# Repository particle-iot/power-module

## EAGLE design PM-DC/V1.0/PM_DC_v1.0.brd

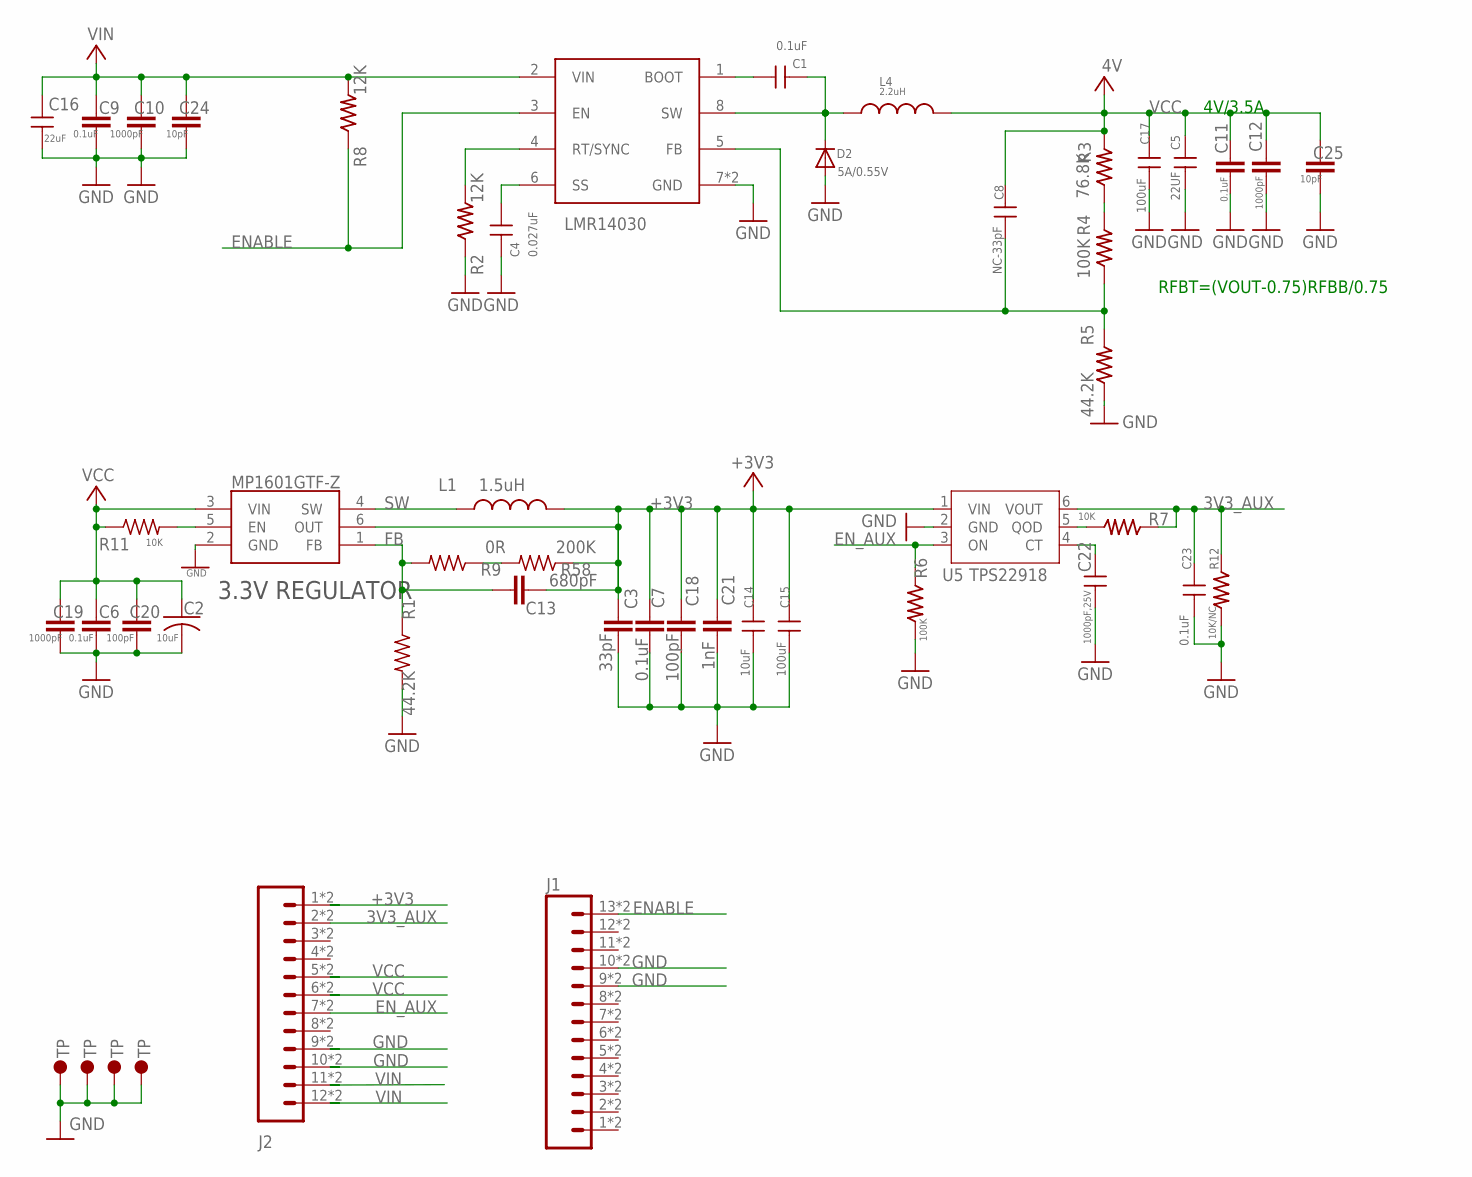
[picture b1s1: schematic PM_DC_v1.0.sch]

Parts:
C1: 0.1uF; C0402
C2: 10uF; C0603_B
C3: 33pF; C0402_B
C4: 0.027uF; C0402
C5: 22UF; C0805
C6, C7, C9, C11: 0.1uF; C0402_B
C8: NC-33pF; C0402
C10, C12, C19: 1000pF; C0402_B
C13: 680pF; C0402_B
C14: 10uF; C0805
C15, C17: 100uF; C1206
C16: 22uF; C805
C18, C20: 100pF; C0402_B
C21: 1nF; C0402_B
C22: 1000pF,25V; C0402
C23: 0.1uF; C-0402
C24, C25: 10pF; C0402_B
D2: 5A/0.55V; SMADIODE
J1: M13PTH-CST-R; 1X13-CASTELLATED
J2: M12PTH-CST-R; 1X12-CASTELLATED
L1: 1.5uH; INDUCTOR-2520
L4: 2.2uH; INDUCTOR-4040
R1: 44.2K; R0402_B
R2, R8: 12K; R-0402S
R3: 76.8K; R-0402S
R4: 100K; R-0402S
R5: 44.2K; R-0402S
R6: 100K; R0402
R7: 10K; R0402
R9: 0R; R0402_B
R11: 10K; R0402_B
R12: 10K/NC; R0402
R58: 200K; R0402_B
U2: LMR14030; SO_POWERPAD_8
U3: MP1601GTF-Z; SOTFL50P160X60-6N
U5: TPS22918; SOT-23-6
U$1, U$2, U$4, U$5: TP; TP_2.33X1.37

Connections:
3V3_AUX: C23.1, J2.2, J2.@2 (2), R7.1, R12.1, U5.6 (VOUT)
+3V3: C3.2, C7.2, C13.1, C14.1, C15.1, C18.2, C21.2, J2.1, J2.@1 (1), L1.2, R58.1, U3.6 (OUT), U5.1 (VIN)
ENABLE: J1.13, J1.@13 (13), R8.1, U2.3 (EN)
EN_AUX: J2.7, J2.@7 (7), R6.1, U5.3 (ON)
FB: C13.2, R1.1, R9.2, U3.1 (FB)
GND: C2.2, C3.1, C4.2, C5.2, C6.1, C7.1, C9.1, C10.1, C11.1, C12.1, C14.2, C15.2, C16.2, C17.2, C18.1, C19.1, C20.1, C21.1, C22.2, C23.2, C24.1, C25.1, D2.A, J1.9, J1.10, J1.@9 (9), J1.@10 (10), J2.9, J2.10, J2.@9 (9), J2.@10 (10), R1.2, R2.1, R5.1, R6.2, R12.2, U2.7 (GND), U2.EP (GND), U3.2 (GND), U5.2 (GND), U$1.1, U$2.1, U$4.1, U$5.1
unnamed: R7.2, U5.5 (QOD)
unnamed: C8.1, R4.1, R5.2, U2.5 (FB)
unnamed: R11.2, U3.5 (EN)
unnamed: R9.1, R58.2
unnamed: C4.1, U2.6 (SS)
unnamed: C1.2, D2.C, L4.P$1 (1), U2.8 (SW)
unnamed: C1.1, U2.1 (BOOT)
unnamed: R2.2, U2.4 (RT/SYNC)
unnamed: R3.1, R4.2
unnamed: C22.1, U5.4 (CT)
SW: L1.1, U3.4 (SW)
VCC: C2.1, C5.1, C6.2, C8.2, C11.2, C12.2, C17.1, C19.2, C20.2, C25.2, J2.5, J2.6, J2.@5 (5), J2.@6 (6), L4.P$2 (2), R3.2, R11.1, U3.3 (VIN)
VIN: C9.2, C10.2, C16.1, C24.2, J2.11, J2.12, J2.@11 (11), J2.@12 (12), R8.2, U2.2 (VIN)

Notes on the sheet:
4V/3.5A
3.3V REGULATOR
RFBT=(VOUT-0.75)RFBB/0.75

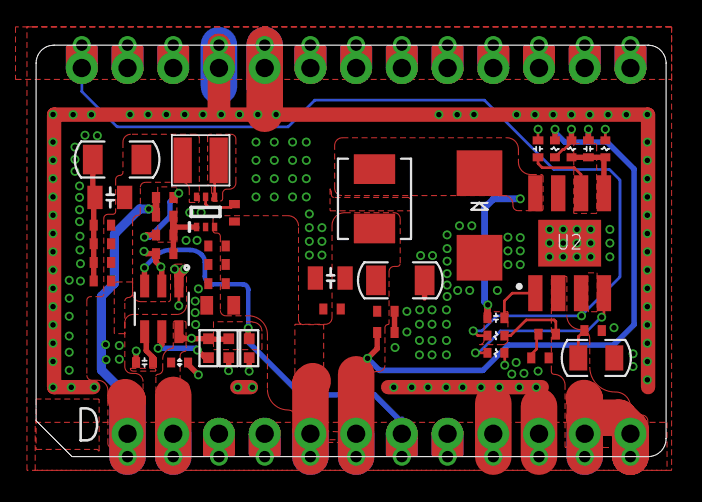
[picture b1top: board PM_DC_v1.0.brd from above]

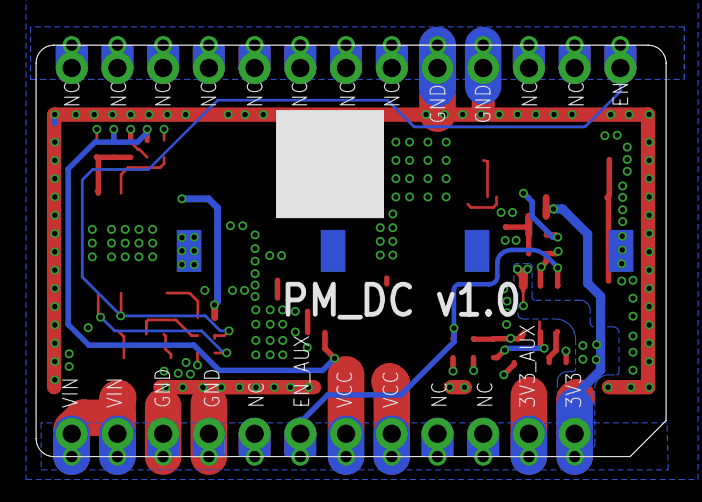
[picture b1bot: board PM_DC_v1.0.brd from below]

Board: 2 copper layers, 35.0 x 22.9 mm, 49 parts (4 on the bottom side), 19 nets.

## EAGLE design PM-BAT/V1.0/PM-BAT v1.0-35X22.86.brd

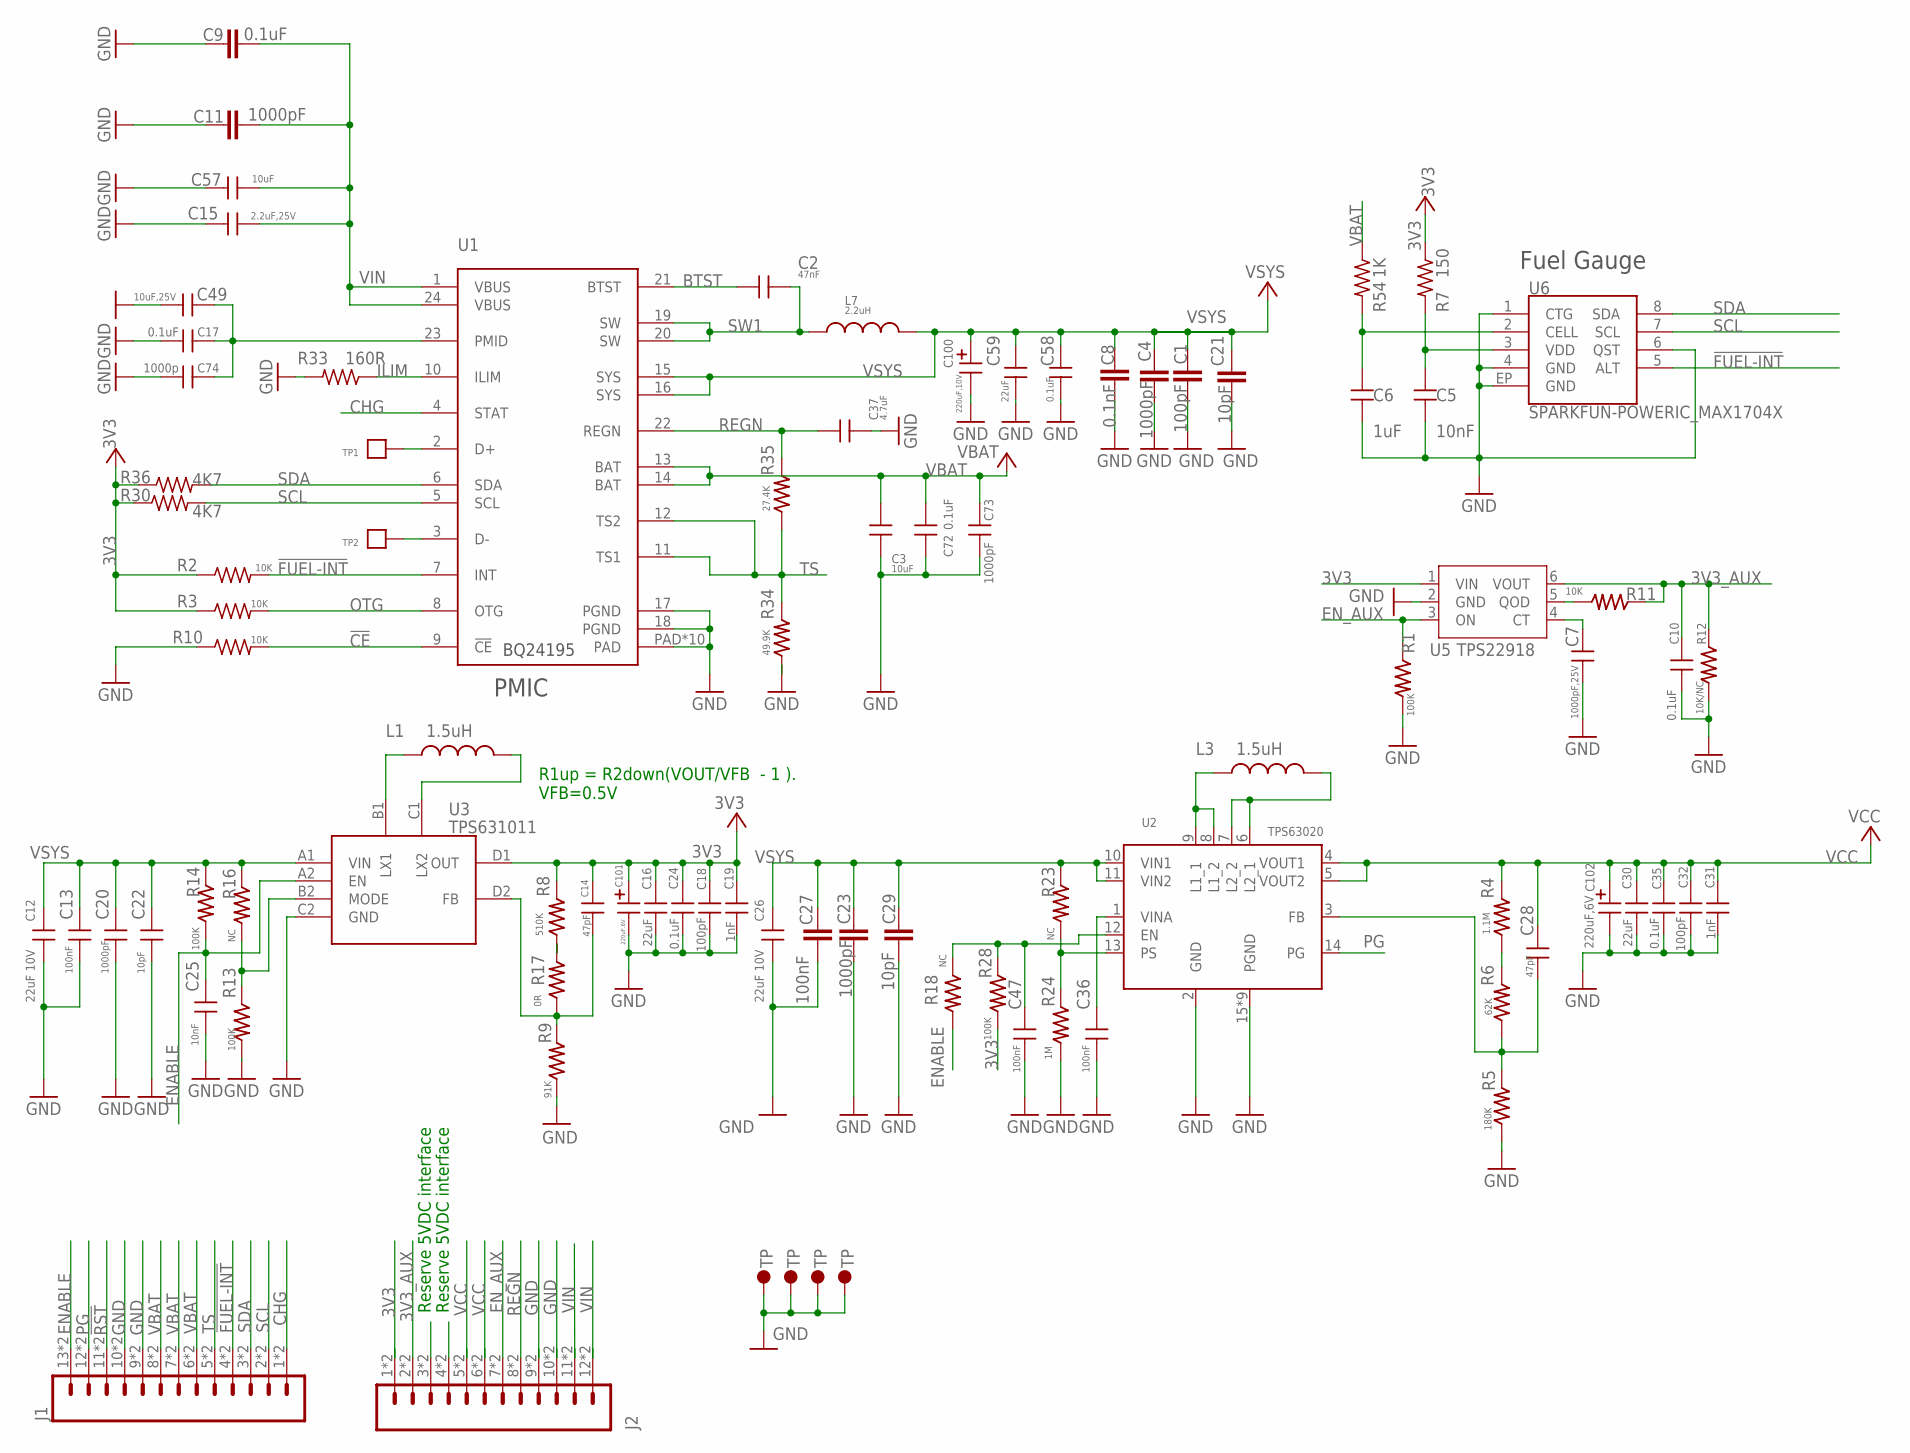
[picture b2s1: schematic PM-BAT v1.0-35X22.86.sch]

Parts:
C1: 100pF; C0402_B
C2: 47nF; C-0402
C3: 10uF; C0805
C4, C11, C23: 1000pF; C0402_B
C5: 10nF; C0402
C6: 1uF; C0402
C7: 1000pF,25V; C0402
C8: 0.1nF; C0402_B
C9: 0.1uF; C0402_B
C10: 0.1uF; C0201-N
C12, C26: 22uF 10V; C0603
C13, C36, C47: 100nF; C0201-N
C14, C28: 47pF; C0201-N
C15: 2.2uF,25V; C-0603A
C16, C30: 22uF; C-0603A
C17, C24, C35, C58: 0.1uF; C0402
C18, C32: 100pF; C0402
C19, C31: 1nF; C0402
C20: 1000pF; C0201-N
C21, C29: 10pF; C0402_B
C22: 10pF; C0201-N
C25: 10nF; C0201-N
C27: 100nF; C0402_B
C37: 4.7uF; C0402
C49: 10uF,25V; C-0603A
C57: 10uF; C-0603A
C59: 22uF; C0603
C72: 0.1uF; C-0402
C73: 1000pF; C-0402
C74: 1000p; C-0402
C100: 220uF,10V; CASE-B
C101: 220uF.6V; CASE-B
C102: 220uF,6V; CASE-B
J1: M13PTH-CST-R; 1X13-CASTELLATED
J2: M12PTH-CST-R; 1X12-CASTELLATED
L1, L3: 1.5uH; INDUCTOR-2520
L7: 2.2uH; INDUCTOR-4040
R1, R13, R14, R28: 100K; R0201-N
R2, R3, R10: 10K; R0402_B
R4: 1.1M; R0201-N
R5: 180K; R0201-N
R6: 62K; R0201-N
R7: 150; R0402_B
R8: 510K; R0201-N
R9: 91K; R0201-N
R11: 10K; R0201-N
R12: 10K/NC; R0201-N
R16, R18, R23: NC; R0201-N
R17: 0R; R0201-N
R24: 1M; R0201-N
R30, R36: 4K7; R0402_B
R33: 160R; R0402_B
R34: 49.9K; R0201-N
R35: 27.4K; R0201-N
R54: 1K; R0402_B
TP1, TP2: TP1311MM; TP-1311MM
U1: BQ24195; ELECTRON_QFN24
U2: TPS63020
U3: TPS631011; DSBGA
U5: TPS22918; SOT-23-6
U6: SPARKFUN-POWERIC_MAX1704X; SPARKFUN-POWERIC_TDFN-8
U$1, U$2, U$4, U$5: TP; TP_2.33X1.37

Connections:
3V3: C14.1, C16.1, C18.1, C19.1, C24.1, C101.P$1 (1), J2.1, J2.@1 (1), R2.1, R3.1, R7.1, R8.2, R28.2, R30.1, R36.1, U3.D1 (OUT), U5.1 (VIN)
3V3_AUX: C10.1, J2.2, J2.@2 (2), R11.1, R12.1, U5.6 (VOUT)
!CE: R10.2, U1.9 (!CE)
!FUEL-INT: J1.4, J1.@4 (4), R2.2, U1.7 (INT), U6.5 (ALT)
!RST: J1.11, J1.@11 (11)
BTST: C2.1, U1.21 (BTST)
CHG: J1.1, J1.@1 (1), U1.4 (STAT)
ENABLE: C25.1, J1.13, J1.@13 (13), R14.2, R18.2, U3.A2 (EN)
EN_AUX: J2.7, J2.@7 (7), R1.1, U5.3 (ON)
GND: C1.1, C3.2, C4.1, C5.2, C6.2, C7.2, C8.1, C9.1, C10.2, C11.1, C12.2, C13.2, C15.2, C16.2, C17.1, C18.2, C19.2, C20.2, C21.1, C22.2, C23.1, C24.2, C25.2, C26.2, C27.1, C29.1, C30.2, C31.2, C32.2, C35.2, C36.2, C37.2, C47.2, C49.2, C57.2, C58.2, C59.2, C72.2, C73.2, C74.1, C100.P$2 (2), C101.P$2 (2), C102.P$2 (2), J1.9, J1.10, J1.@9 (9), J1.@10 (10), J2.9, J2.10, J2.@9 (9), J2.@10 (10), R1.2, R5.1, R9.1, R10.1, R12.2, R13.2, R24.2, R33.2, R34.1, U1.17 (PGND), U1.18 (PGND), U1.PAD, U1.PAD@1 (PAD), U1.PAD@2 (PAD), U1.PAD@3 (PAD), U1.PAD@4 (PAD), U1.PAD@5 (PAD), U1.PAD@6 (PAD), U1.PAD@7 (PAD), U1.PAD@8 (PAD), U1.PAD@9 (PAD), U2.2 (GND), U2.15 (PGND), U2.16 (PGND), U2.17 (PGND), U2.18 (PGND), U2.19 (PGND), U2.20 (PGND), U2.21 (PGND), U2.22 (PGND), U2.23 (PGND), U3.C2 (GND), U5.2 (GND), U6.1 (CTG), U6.4 (GND), U6.6 (QST), U6.EP (GND), U$1.1, U$2.1, U$4.1, U$5.1
ILIM: R33.1, U1.10 (ILIM)
unnamed: J2.3, J2.@3 (3)
unnamed: C17.2, C49.1, C74.2, U1.23 (PMID)
unnamed: TP2.P$1, U1.3 (D-)
unnamed: C14.2, R9.2, R17.1, U3.D2 (FB)
unnamed: C28.2, R5.2, R6.1, U2.3 (FB)
unnamed: TP1.P$1, U1.2 (D+)
unnamed: R8.1, R17.2
unnamed: R4.1, R6.2
unnamed: J2.4, J2.@4 (4)
unnamed: L3.1, U2.8 (L1_2), U2.9 (L1_1)
unnamed: L1.1, U3.B1 (LX1)
unnamed: R13.1, R16.2, U3.B2 (MODE)
unnamed: L3.2, U2.6 (L2_1), U2.7 (L2_2)
unnamed: L1.2, U3.C1 (LX2)
unnamed: C7.1, U5.4 (CT)
unnamed: C36.1, U2.1 (VINA)
unnamed: R11.2, U5.5 (QOD)
unnamed: C47.1, R18.1, R28.1, U2.12 (EN)
unnamed: R23.2, R24.1, U2.13 (PS)
unnamed: C5.1, R7.2, U6.3 (VDD)
unnamed: C6.1, R54.2, U6.2 (CELL)
OTG: R3.2, U1.8 (OTG)
PG: J1.12, J1.@12 (12), U2.14 (PG)
REGN: C37.1, J2.8, J2.@8 (8), R35.2, U1.22 (REGN)
SCL: J1.2, J1.@2 (2), R30.2, U1.5 (SCL), U6.7 (SCL)
SDA: J1.3, J1.@3 (3), R36.2, U1.6 (SDA), U6.8 (SDA)
SW1: C2.2, L7.P$1 (1), U1.19 (SW), U1.20 (SW)
TS: J1.5, J1.@5 (5), R34.2, R35.1, U1.11 (TS1), U1.12 (TS2)
VBAT: C3.1, C72.1, C73.1, J1.6, J1.7, J1.8, J1.@6 (6), J1.@7 (7), J1.@8 (8), R54.1, U1.13 (BAT), U1.14 (BAT)
VCC: C28.1, C30.1, C31.1, C32.1, C35.1, C102.P$1 (1), J2.5, J2.6, J2.@5 (5), J2.@6 (6), R4.2, U2.4 (VOUT1), U2.5 (VOUT2)
VIN: C9.2, C11.2, C15.1, C57.1, J2.11, J2.12, J2.@11 (11), J2.@12 (12), U1.1 (VBUS), U1.24 (VBUS)
VSYS: C1.2, C4.2, C8.2, C12.1, C13.1, C20.1, C21.2, C22.1, C23.2, C26.1, C27.2, C29.2, C58.1, C59.1, C100.P$1 (1), L7.P$2 (2), R14.1, R16.1, R23.1, U1.15 (SYS), U1.16 (SYS), U2.10 (VIN1), U2.11 (VIN2), U3.A1 (VIN)

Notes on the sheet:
PMIC
Fuel Gauge
R1up = R2down(VOUT/VFB - 1 ). VFB=0.5V
Reserve 5VDC interface

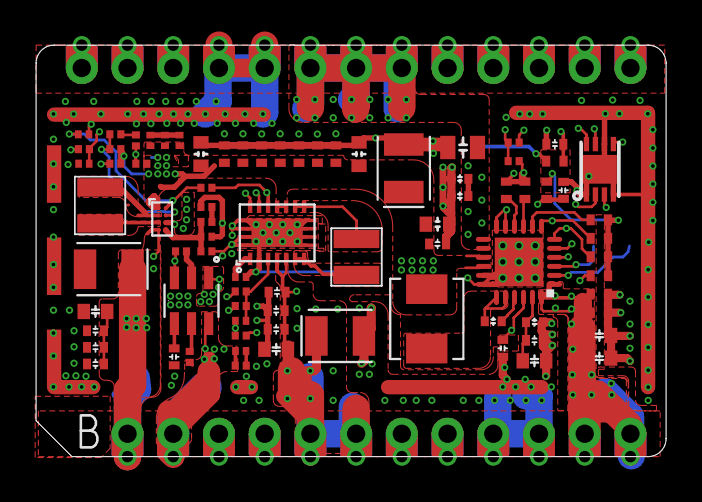
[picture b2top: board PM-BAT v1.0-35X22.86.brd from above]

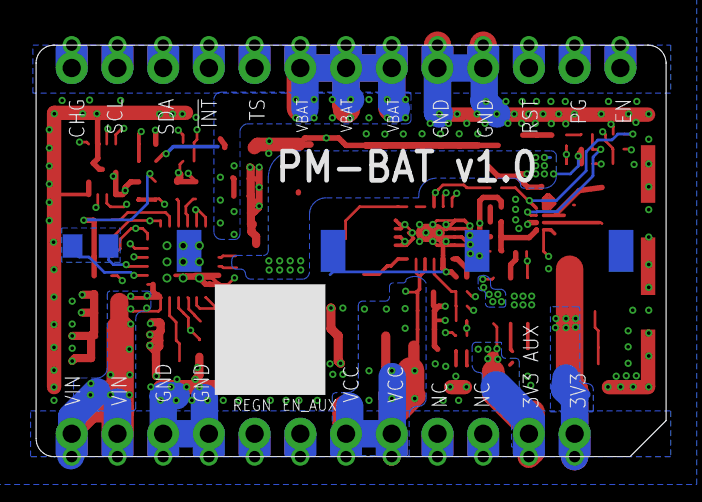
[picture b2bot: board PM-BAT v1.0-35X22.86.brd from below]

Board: 4 copper layers, 35.0 x 22.9 mm, 88 parts (6 on the bottom side), 43 nets.

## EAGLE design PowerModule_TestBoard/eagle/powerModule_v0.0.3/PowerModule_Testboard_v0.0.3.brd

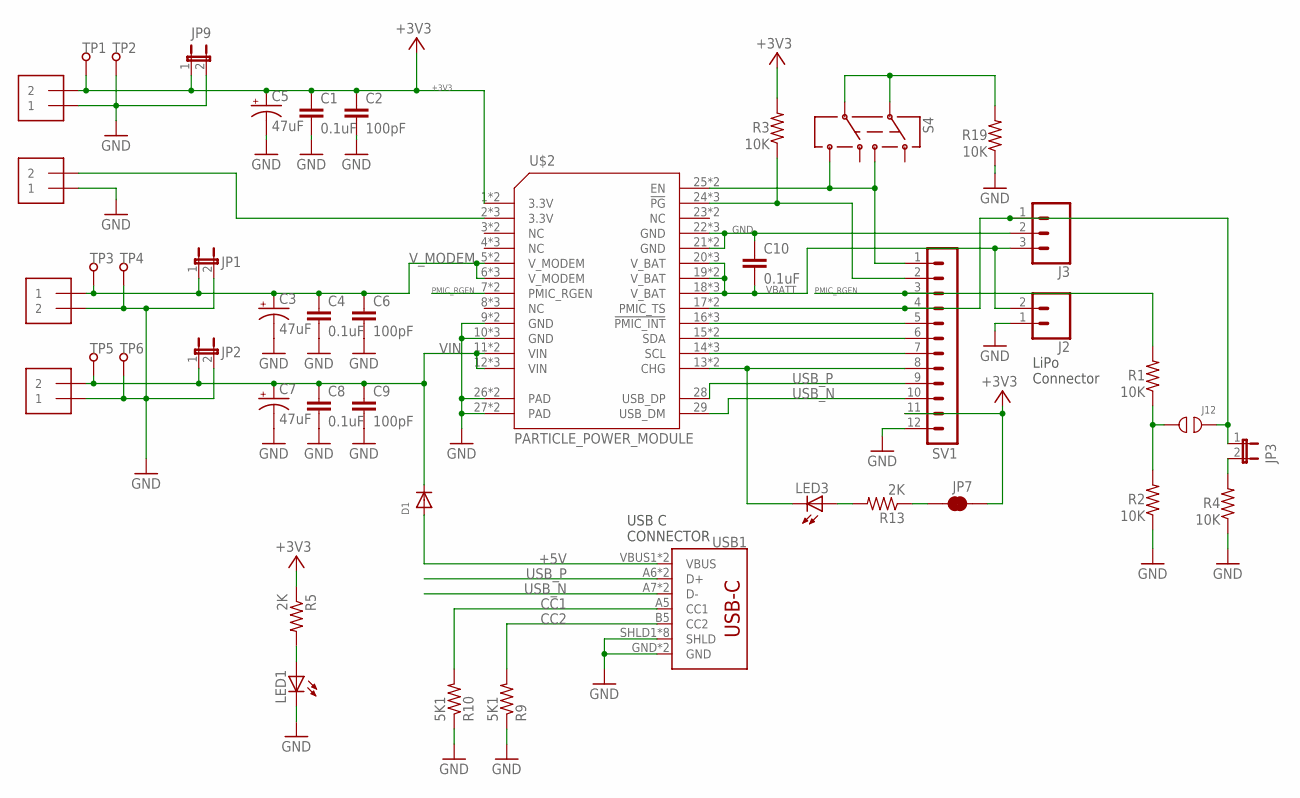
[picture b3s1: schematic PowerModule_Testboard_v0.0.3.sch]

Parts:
C1, C4, C8, C10: 0.1uF; 0603
C2, C6, C9: 100pF; 0603
C3, C5, C7: 47uF; NIC_10X10.5_CAP
D1: DIODE_SOD-123FL; SOD-123FL
J1, J4, J5, J6: 1X2-3.5MM
J2: CONN_02-JST-2MM-SMT; JST-2-SMD@2
J3: CONN_03JST-SMD-VERT; JST-3-SMD-VERT
J12: TP_OPEN
JP1, JP2, JP3, JP9: JUMPER2
JP7: JUMPER-SMT_2_NC_TRACE_NO-SILK; SMT-JUMPER_2_NC_TRACE_NO-SILK
LED1, LED3: LEDCHIP-LED0603; CHIP-LED0603
R1, R2, R3, R4, R19: 10K; R0603_P
R5, R13: 2K; R0603_P
R9, R10: 5K1; R0603_P
S4: SWITCH-DPDT; SWITCH-2.5X3.2-6
SV1: MA12-1
TP1, TP2, TP3, TP4, TP5, TP6: TP-S2751-46R; S2751-46R
U$2: PARTICLE_POWER_MODULE
USB1: USB_C16PIN; USB-C-16P

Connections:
+3V3: C1.1, C2.1, C5.+, J4.2, JP7.1, JP9.1, R3.2, R5.1, SV1.11, TP1.1, U$2.1 (3.3V), U$2.1@1 (3.3V)
+5V: D1.A, USB1.VBUS1 (VBUS), USB1.VBUS2 (VBUS)
CC1: R10.2, USB1.A5 (CC1)
CC2: R9.2, USB1.B5 (CC2)
GND: C1.2, C2.2, C3.-, C4.2, C5.-, C6.2, C7.-, C8.2, C9.2, C10.1, J1.2, J2.1 (2), J3.2, J4.1, J5.1, J6.1, JP1.2, JP2.2, JP9.2, LED1.C, R2.1, R4.1, R9.1, R10.1, R19.1, SV1.12, TP2.1, TP4.1, TP6.1, U$2.9 (GND), U$2.9@1 (GND), U$2.10 (GND), U$2.10@1 (GND), U$2.10@2 (GND), U$2.21 (GND), U$2.21@1 (GND), U$2.22 (GND), U$2.22@1 (GND), U$2.22@2 (GND), U$2.26 (PAD), U$2.26@1 (PAD), U$2.27 (PAD), U$2.27@2 (PAD), USB1.GND, USB1.GND2 (GND), USB1.SHLD1 (SHLD), USB1.SHLD2 (SHLD), USB1.SHLD3 (SHLD), USB1.SHLD4 (SHLD), USB1.SHLD5 (SHLD), USB1.SHLD6 (SHLD), USB1.SHLD7 (SHLD), USB1.SHLD8 (SHLD)
unnamed: JP7.2, R13.1
unnamed: R19.2, S4.2, S4.5
unnamed: J12.1, R1.1, R2.2
unnamed: R3.1, SV1.2, U$2.24 (!PG), U$2.24@1 (!PG), U$2.24@2 (!PG)
unnamed: J3.1, J12.2, JP3.1, SV1.4, U$2.17 (PMIC_TS), U$2.17@1 (PMIC_TS)
unnamed: SV1.5, U$2.16 (!PMIC_INT), U$2.16@1 (!PMIC_INT), U$2.16@2 (!PMIC_INT)
unnamed: SV1.6, U$2.15 (SDA), U$2.15@1 (SDA)
unnamed: SV1.7, U$2.14 (SCL), U$2.14@1 (SCL), U$2.14@2 (SCL)
unnamed: JP3.2, R4.2
unnamed: LED3.C, SV1.8, U$2.13 (CHG), U$2.13@1 (CHG)
unnamed: LED3.A, R13.2
unnamed: S4.3, S4.6, SV1.1, U$2.25 (EN), U$2.25@1 (EN)
unnamed: J6.2, U$2.2 (3.3V), U$2.2@1 (3.3V), U$2.2@2 (3.3V)
unnamed: LED1.A, R5.2
PMIC_RGEN: R1.2, SV1.3, U$2.7 (PMIC_RGEN), U$2.7@1 (PMIC_RGEN)
USB_N: SV1.10, U$2.29 (USB_DM), USB1.A7 (D-), USB1.B7 (D-)
USB_P: SV1.9, U$2.28 (USB_DP), USB1.A6 (D+), USB1.B6 (D+)
VBATT: C10.2, J2.2 (1), J3.3, U$2.18 (V_BAT), U$2.18@1 (V_BAT), U$2.18@2 (V_BAT), U$2.19 (V_BAT), U$2.19@1 (V_BAT), U$2.20 (V_BAT), U$2.20@1 (V_BAT), U$2.20@2 (V_BAT)
VIN: C7.+, C8.1, C9.1, D1.C, J5.2, JP2.1, TP5.1, U$2.11 (VIN), U$2.11@1 (VIN), U$2.12 (VIN), U$2.12@1 (VIN), U$2.12@2 (VIN)
V_MODEM: C3.+, C4.1, C6.1, J1.1, JP1.1, TP3.1, U$2.5 (V_MODEM), U$2.5@1 (V_MODEM), U$2.6 (V_MODEM), U$2.6@1 (V_MODEM), U$2.6@2 (V_MODEM)

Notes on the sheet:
USB C CONNECTOR
LiPo Connector

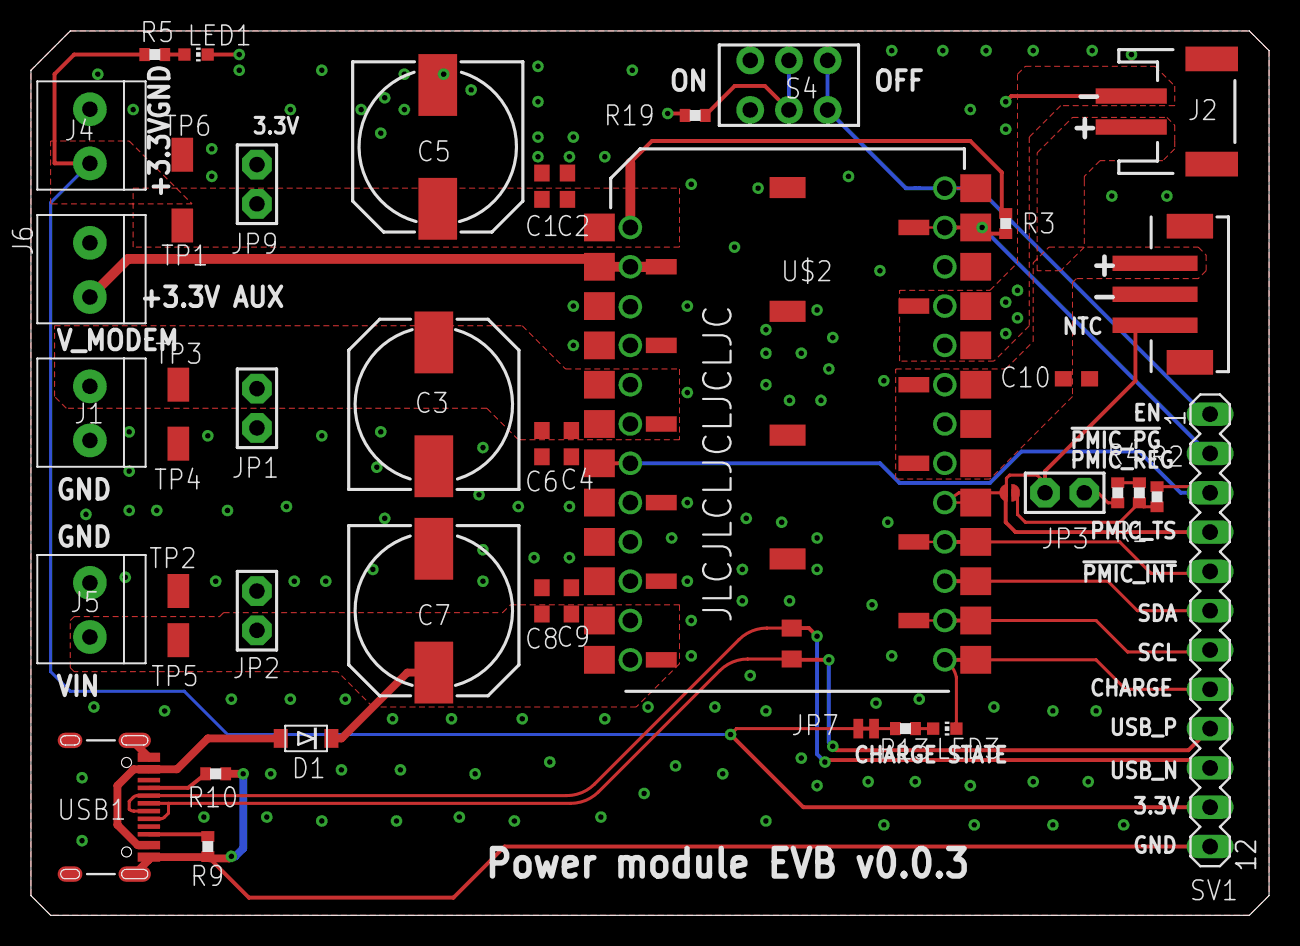
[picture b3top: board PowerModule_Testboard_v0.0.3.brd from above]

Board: 2 copper layers, 80.0 x 57.1 mm, 44 parts (0 on the bottom side), 25 nets.

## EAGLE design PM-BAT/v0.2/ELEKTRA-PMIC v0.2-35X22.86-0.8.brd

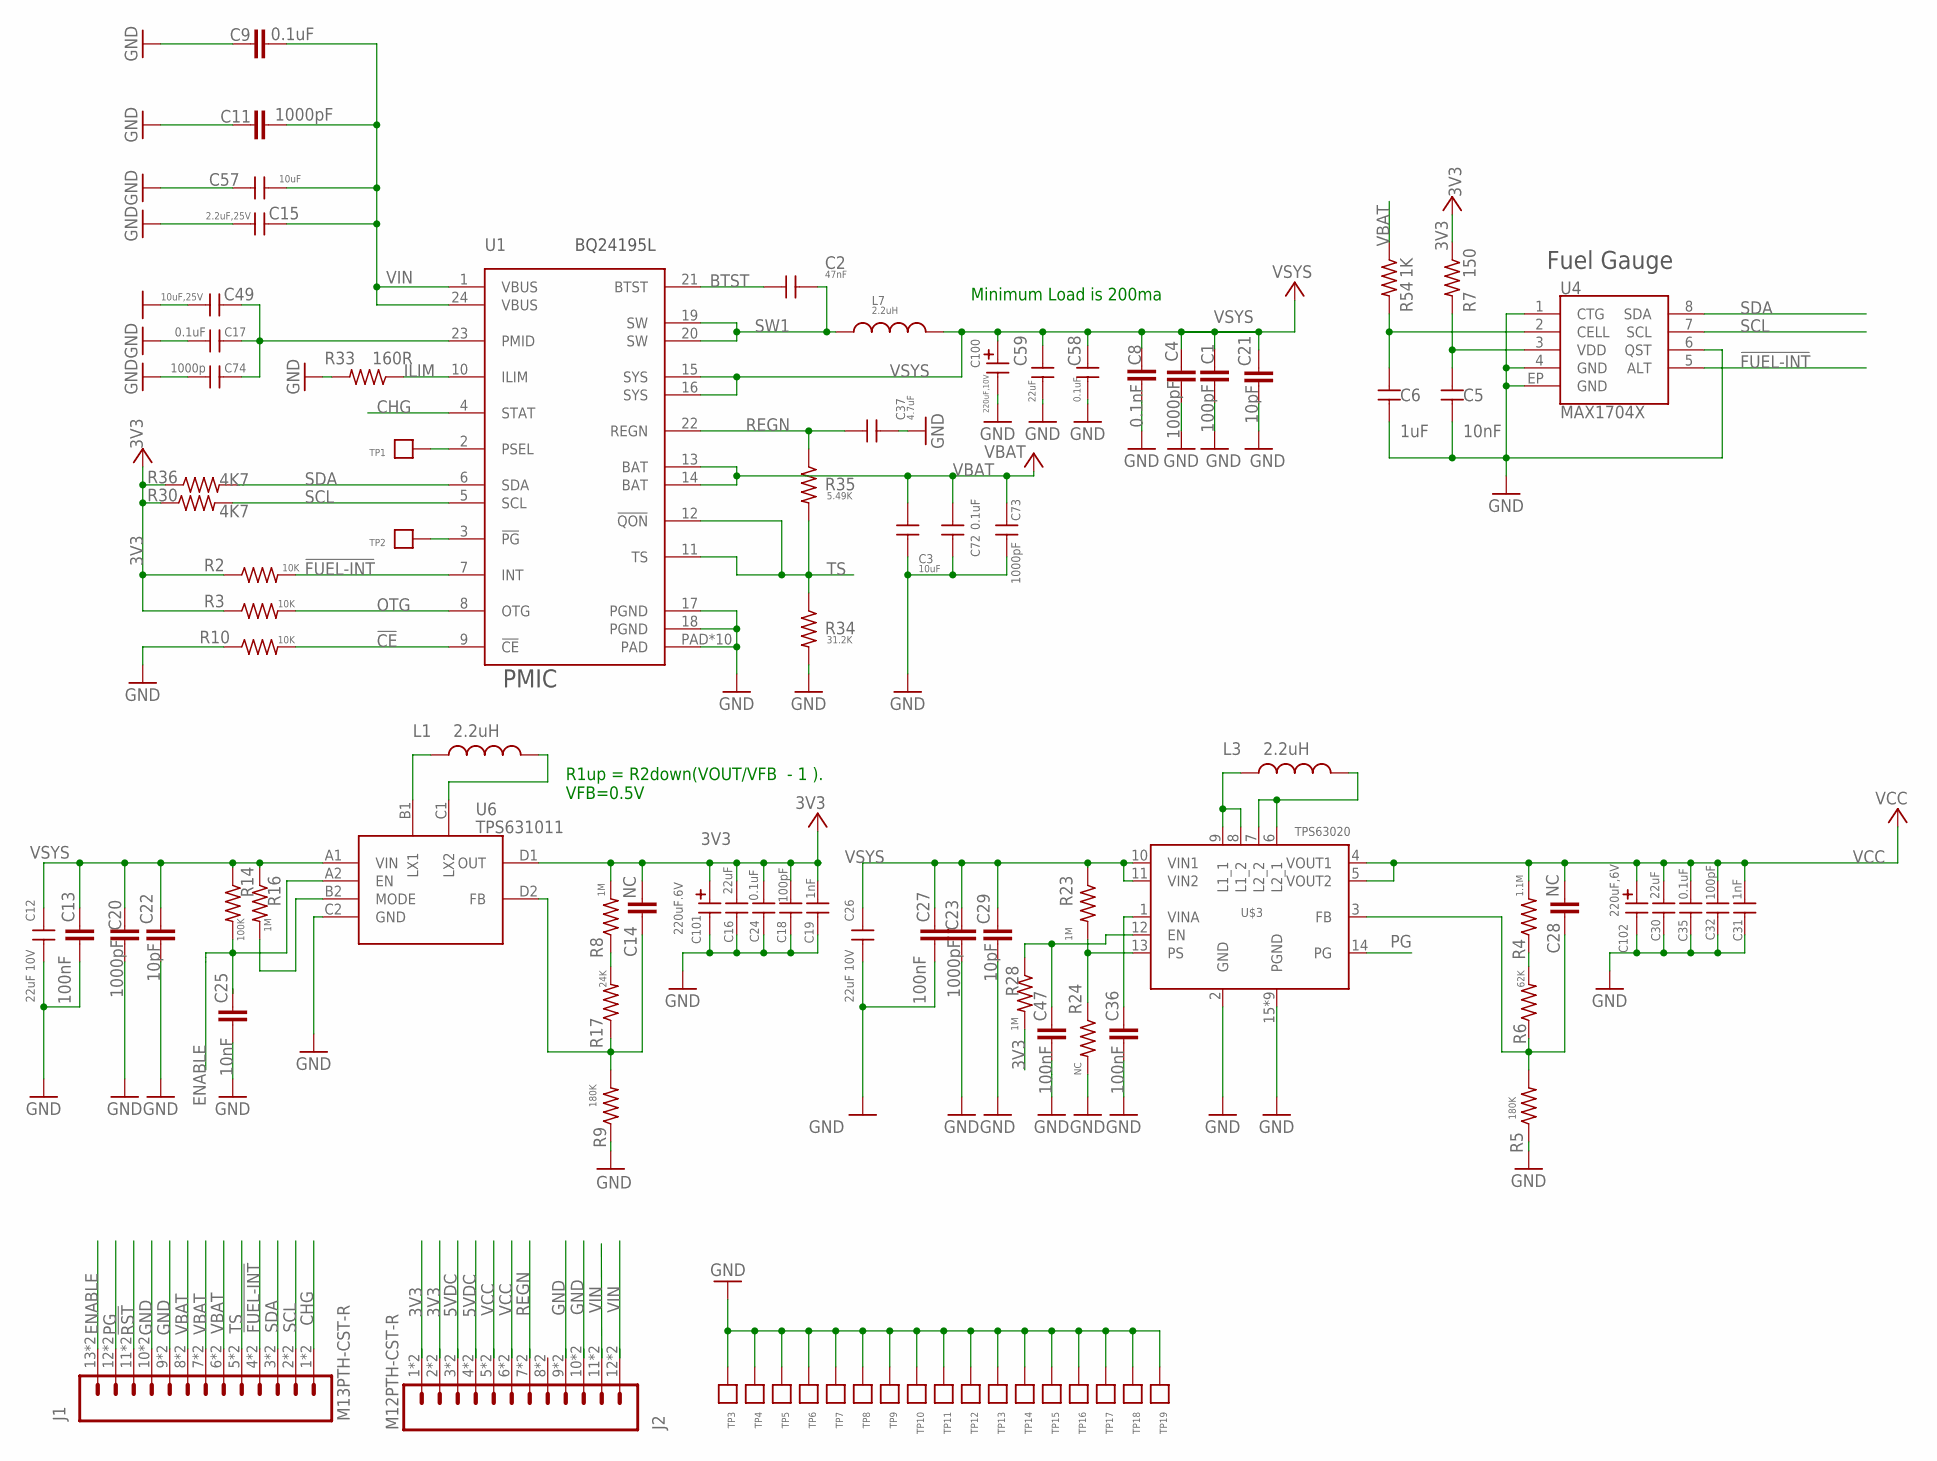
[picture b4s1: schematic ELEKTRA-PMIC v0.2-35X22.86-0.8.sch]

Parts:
C1: 100pF; C0402_B
C2: 47nF; C-0402
C3: 10uF; C0805
C4, C11, C20, C23: 1000pF; C0402_B
C5: 10nF; C0402
C6: 1uF; C0402
C8: 0.1nF; C0402_B
C9: 0.1uF; C0402_B
C12, C26: 22uF 10V; C0805
C13, C27, C36, C47: 100nF; C0402_B
C14, C28: NC; C0402_B
C15: 2.2uF,25V; C-0603A
C16, C30: 22uF; C-0603A
C17, C24, C35, C58: 0.1uF; C0402
C18, C32: 100pF; C0402
C19, C31: 1nF; C0402
C21, C22, C29: 10pF; C0402_B
C25: 10nF; C0402_B
C37: 4.7uF; C0402
C49: 10uF,25V; C-0603A
C57: 10uF; C-0603A
C59: 22uF; C0603
C72: 0.1uF; C-0402
C73: 1000pF; C-0402
C74: 1000p; C-0402
C100: 220uF,10V; CASE-B
C101: 220uF.6V; CASE-B
C102: 220uF,6V; CASE-B
J1: M13PTH-CST-R; 1X13-CASTELLATED
J2: M12PTH-CST-R; 1X12-CASTELLATED
L1, L3: 2.2uH; INDUCTOR-VLS-E
L7: 2.2uH; INDUCTOR-4040
R2, R3, R10: 10K; R0402_B
R4: 1.1M; R0402_B
R5, R9: 180K; R0402_B
R6: 62K; R0402_B
R7: 150; R0402_B
R8, R16, R23, R28: 1M; R0402_B
R14: 100K; R0402_B
R17: 24K; R0402_B
R24: NC; R0402_B
R30, R36: 4K7; R0402_B
R33: 160R; R0402_B
R34: 31.2K; R0402_B
R35: 5.49K; R0402_B
R54: 1K; R0402_B
TP1, TP2: TP1311MM; TP-1311MM
TP3, TP4, TP5, TP6, TP7, TP8, TP9, TP10, TP11, TP12, TP13, TP14, TP15, TP16, TP17, TP18, TP19: TP0.4MM
U1: BQ24195L; QFN24
U4: MAX1704X; TDFN-8
U6: TPS631011; DSBGA
U$3: TPS63020

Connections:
3V3: C14.2, C16.1, C18.1, C19.1, C24.1, C101.P$1 (1), J2.1, J2.2, J2.@1 (1), J2.@2 (2), R2.1, R3.1, R7.1, R8.2, R28.2, R30.1, R36.1, U6.D1 (OUT)
5VDC: J2.3, J2.4, J2.@3 (3), J2.@4 (4)
!CE: R10.2, U1.9 (!CE)
!FUEL-INT: J1.4, J1.@4 (4), R2.2, U1.7 (INT), U4.5 (ALT)
!RST: J1.11, J1.@11 (11)
BTST: C2.1, U1.21 (BTST)
CHG: J1.1, J1.@1 (1), U1.4 (STAT)
ENABLE: C25.2, J1.13, J1.@13 (13), R14.2, U6.A2 (EN)
GND: C1.1, C3.2, C4.1, C5.2, C6.2, C8.1, C9.1, C11.1, C12.2, C13.1, C15.2, C16.2, C17.1, C18.2, C19.2, C20.1, C21.1, C22.1, C23.1, C24.2, C25.1, C26.2, C27.1, C29.1, C30.2, C31.2, C32.2, C35.2, C36.1, C37.2, C47.1, C49.2, C57.2, C58.2, C59.2, C72.2, C73.2, C74.1, C100.P$2 (2), C101.P$2 (2), C102.P$2 (2), J1.9, J1.10, J1.@9 (9), J1.@10 (10), J2.9, J2.10, J2.@9 (9), J2.@10 (10), R5.1, R9.1, R10.1, R24.2, R33.2, R34.2, TP3.P$1, TP4.P$1, TP5.P$1, TP6.P$1, TP7.P$1, TP8.P$1, TP9.P$1, TP10.P$1, TP11.P$1, TP12.P$1, TP13.P$1, TP14.P$1, TP15.P$1, TP16.P$1, TP17.P$1, TP18.P$1, TP19.P$1, U1.17 (PGND), U1.18 (PGND), U1.PAD, U1.PAD@1 (PAD), U1.PAD@2 (PAD), U1.PAD@3 (PAD), U1.PAD@4 (PAD), U1.PAD@5 (PAD), U1.PAD@6 (PAD), U1.PAD@7 (PAD), U1.PAD@8 (PAD), U1.PAD@9 (PAD), U4.1 (CTG), U4.4 (GND), U4.6 (QST), U4.EP (GND), U6.C2 (GND), U$3.2 (GND), U$3.15 (PGND), U$3.16 (PGND), U$3.17 (PGND), U$3.18 (PGND), U$3.19 (PGND), U$3.20 (PGND), U$3.21 (PGND), U$3.22 (PGND), U$3.23 (PGND)
ILIM: R33.1, U1.10 (ILIM)
unnamed: C17.2, C49.1, C74.2, U1.23 (PMID)
unnamed: TP2.P$1, U1.3 (!PG)
unnamed: C14.1, R9.2, R17.1, U6.D2 (FB)
unnamed: C28.1, R5.2, R6.1, U$3.3 (FB)
unnamed: TP1.P$1, U1.2 (PSEL)
unnamed: R8.1, R17.2
unnamed: R4.1, R6.2
unnamed: L3.P$1 (1), U$3.8 (L1_2), U$3.9 (L1_1)
unnamed: L1.P$1 (1), U6.B1 (LX1)
unnamed: R16.2, U6.B2 (MODE)
unnamed: L3.P$2 (2), U$3.6 (L2_1), U$3.7 (L2_2)
unnamed: L1.P$2 (2), U6.C1 (LX2)
unnamed: C36.2, U$3.1 (VINA)
unnamed: C47.2, R28.1, U$3.12 (EN)
unnamed: R23.2, R24.1, U$3.13 (PS)
unnamed: C5.1, R7.2, U4.3 (VDD)
unnamed: C6.1, R54.2, U4.2 (CELL)
OTG: R3.2, U1.8 (OTG)
PG: J1.12, J1.@12 (12), U$3.14 (PG)
REGN: C37.1, J2.7, J2.@7 (7), R35.1, U1.22 (REGN)
SCL: J1.2, J1.@2 (2), R30.2, U1.5 (SCL), U4.7 (SCL)
SDA: J1.3, J1.@3 (3), R36.2, U1.6 (SDA), U4.8 (SDA)
SW1: C2.2, L7.P$1 (1), U1.19 (SW), U1.20 (SW)
TS: J1.5, J1.@5 (5), R34.1, R35.2, U1.11 (TS), U1.12 (!QON)
VBAT: C3.1, C72.1, C73.1, J1.6, J1.7, J1.8, J1.@6 (6), J1.@7 (7), J1.@8 (8), R54.1, U1.13 (BAT), U1.14 (BAT)
VCC: C28.2, C30.1, C31.1, C32.1, C35.1, C102.P$1 (1), J2.5, J2.6, J2.@5 (5), J2.@6 (6), R4.2, U$3.4 (VOUT1), U$3.5 (VOUT2)
VIN: C9.2, C11.2, C15.1, C57.1, J2.11, J2.12, J2.@11 (11), J2.@12 (12), U1.1 (VBUS), U1.24 (VBUS)
VSYS: C1.2, C4.2, C8.2, C12.1, C13.2, C20.2, C21.2, C22.2, C23.2, C26.1, C27.2, C29.2, C58.1, C59.1, C100.P$1 (1), L7.P$2 (2), R14.1, R16.1, R23.1, U1.15 (SYS), U1.16 (SYS), U6.A1 (VIN), U$3.10 (VIN1), U$3.11 (VIN2)

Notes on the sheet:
Minimum Load is 200ma
PMIC
Fuel Gauge
R1up = R2down(VOUT/VFB - 1 ). VFB=0.5V

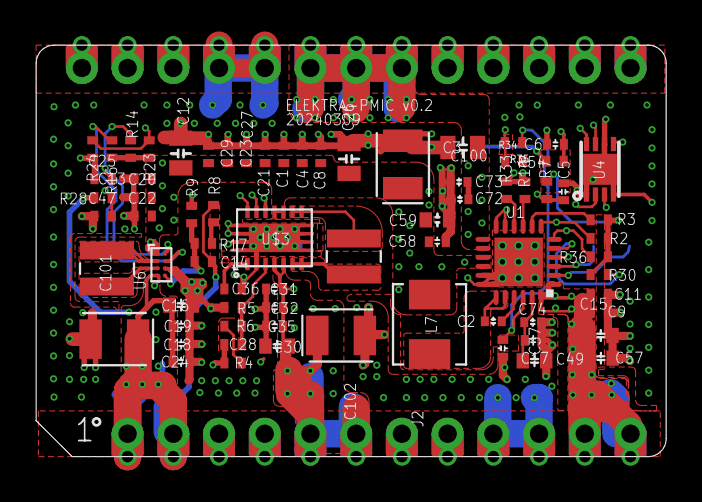
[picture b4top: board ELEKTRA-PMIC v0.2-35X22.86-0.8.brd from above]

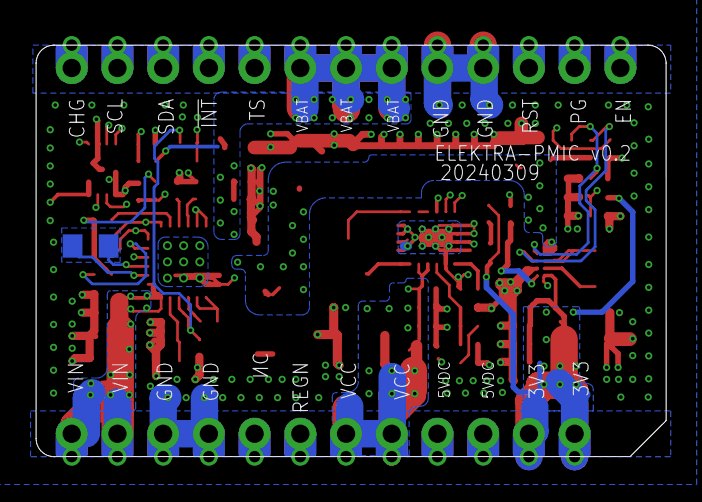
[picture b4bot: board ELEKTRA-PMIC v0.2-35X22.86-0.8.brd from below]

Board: 4 copper layers, 35.0 x 22.9 mm, 93 parts (19 on the bottom side), 38 nets.

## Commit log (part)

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2024-01-04 add sch and pcb
2024-01-12 Design elektra PMIC and Bench modules
2024-02-01 upload PCB and sch
    upload PCB and sch
2024-03-06 Placement
    modify the one of DC_DC and pcb size
2024-03-08 update palcement
    make the two connector 0.8inch
2024-03-08 update
    layout
2024-03-09 update layout
    complete the layout for power module
2024-03-11 update layout
    Optimize routing
2024-03-11 update
    complete layout
2024-03-12 add change list
    add change list
2024-03-14 update the schematic for power module
2024-03-14 change the name for test board
2024-03-15 update the power module
2024-03-21 update the design for power module test board and generate the gerber
2024-03-23 Delete ELEKTRA-PMIC/V0.2 directory
    this is just a PCB placement for review ,it is not needed right now
2024-03-23 Update
    Change PCB silkscreen
    Add GND pad
    Add tranker code location
2024-03-23 add gerber
    add gerber
2024-03-25 update the design file
2024-04-03 Update SCH&PCB
    V0.4 Change list:
    1. Add resistor R13
    2. Add load switch circuit U5
    3. An EN_AUX PIN is added to the NC of the connector to control the load switch, and the position of the REGN pin is exchanged to better layout
    4. Update R9, R18, R17 parameters
    5. Some resistors are changed to 0201 footprint
2024-04-03 update PM_DC
2024-04-03 update
    change the name as PM-BAT
2024-04-10 update
    add shield case DXF
2024-04-15 update
    1.add load Switch IC
    2.change some footprint 0201 as 0401
    3.re-placement and re-layout
2024-04-15 update
    Optimize layout
2024-04-24 update
    output gerber for MO DFM
2024-04-26 update
    update
2024-04-30 updae
    1.Increase the distance between the shield and the connector
    2.Modify silk screen mark
    3.for PM-DC:Change the inductor and diode to lower the height
2024-05-06 update
    update and output DXF for DFM
2024-06-03 upload xydate and placement and update based test
2024-08-01 Create v1.0 file
2024-08-02 Adjust the version silkscreen position.
2025-08-20 Add CC-BY-SA license

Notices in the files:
parts and their libraries:
SparkFun-PowerIC: Licensing: Creative Commons ShareAlike 4.0 International - https://creativecommons.org/licenses/by-sa/4.0
microbuilder: This work is placed in the public domain, and may be freely used for commercial and non-commercial work with the following conditions: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
